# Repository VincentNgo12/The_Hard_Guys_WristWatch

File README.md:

View this project on [CADLAB.io](https://cadlab.io/project/29861). 

# Smart Wristwatch - The Hard Guys team

PCB schematics and hardware design for an ESP32-based wearable health and safety system.
This repository contains schematic capture, power architecture, and sensor integration
for a modular embedded prototype developed during a 48-hour hackathon.

> Status: Early schematic design

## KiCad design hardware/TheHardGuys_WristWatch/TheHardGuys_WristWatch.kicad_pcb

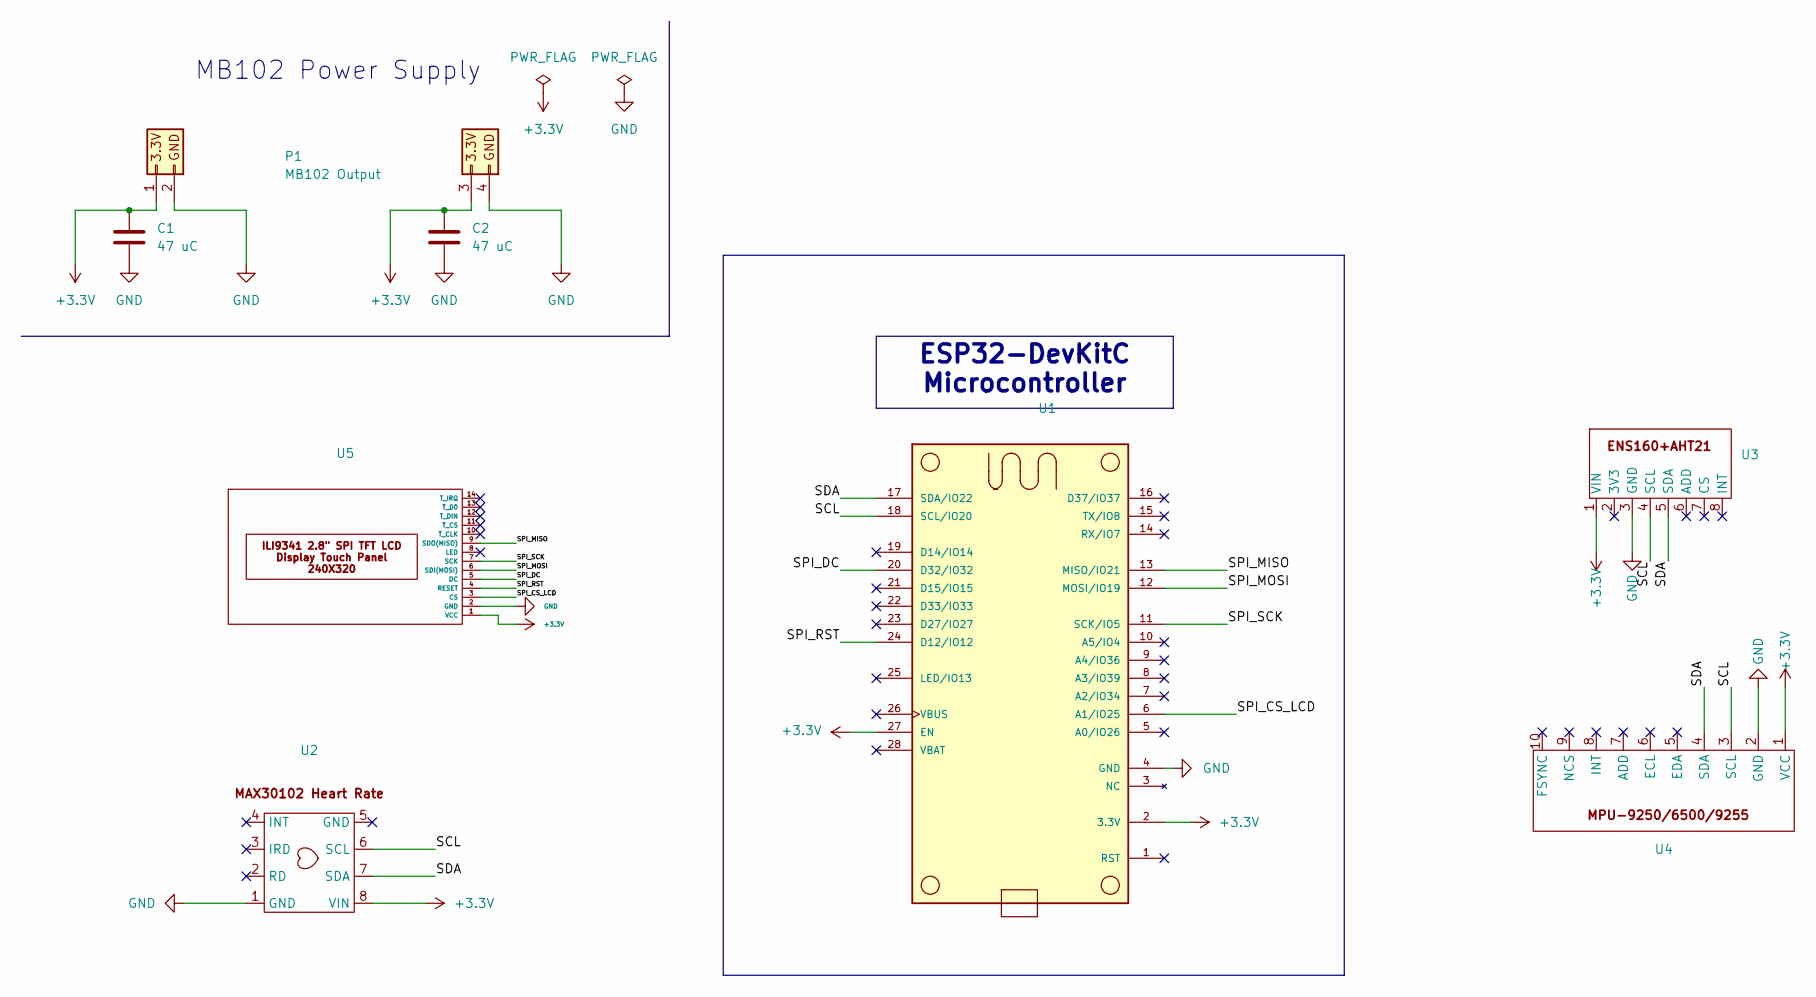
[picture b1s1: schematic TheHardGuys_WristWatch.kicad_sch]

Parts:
C1, C2: 47 uC; CP_Radial_D6.3mm_P2.50mm
P1: MB102 Output; MB102_Breadboard_Power_Module
U1: ESP32_Feather_V2
U2: MAX30102 Heart Rate_Pulse Sensor
U3: ENS160+AHT21_Environmental_Sensor
U4: MPU6500_IMU
U5: ILI9341_2.8__SPI_TFT_LCD

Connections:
+3.3V: C1.1, C2.1, P1.1 (3.3V), P1.3 (3.3V), U1.2 (3.3V), U1.27 (EN), U2.8 (VIN), U3.1 (VIN), U4.1 (VCC), U5.1 (VCC)
/SCL: U1.18 (SCL/IO20), U2.6 (SCL), U3.4 (SCL), U4.3 (SCL)
/SDA: U1.17 (SDA/IO22), U2.7 (SDA), U3.5 (SDA), U4.4 (SDA)
/SPI_CS_LCD: U1.6 (A1/IO25), U5.3 (CS)
/SPI_DC: U1.20 (D32/IO32), U5.5 (DC)
/SPI_MISO: U1.13 (MISO/IO21), U5.9 (SDO(MISO))
/SPI_MOSI: U1.12 (MOSI/IO19), U5.6 (SDI(MOSI))
/SPI_RST: U1.24 (D12/IO12), U5.4 (RESET)
/SPI_SCK: U1.11 (SCK/IO5), U5.7 (SCK)
GND: C1.2, C2.2, P1.2 (GND), P1.4 (GND), U1.4 (GND), U2.1 (GND), U3.3 (GND), U4.2 (GND), U5.2 (GND)

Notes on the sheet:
MB102 Power Supply
ESP32-DevKitC Microcontroller

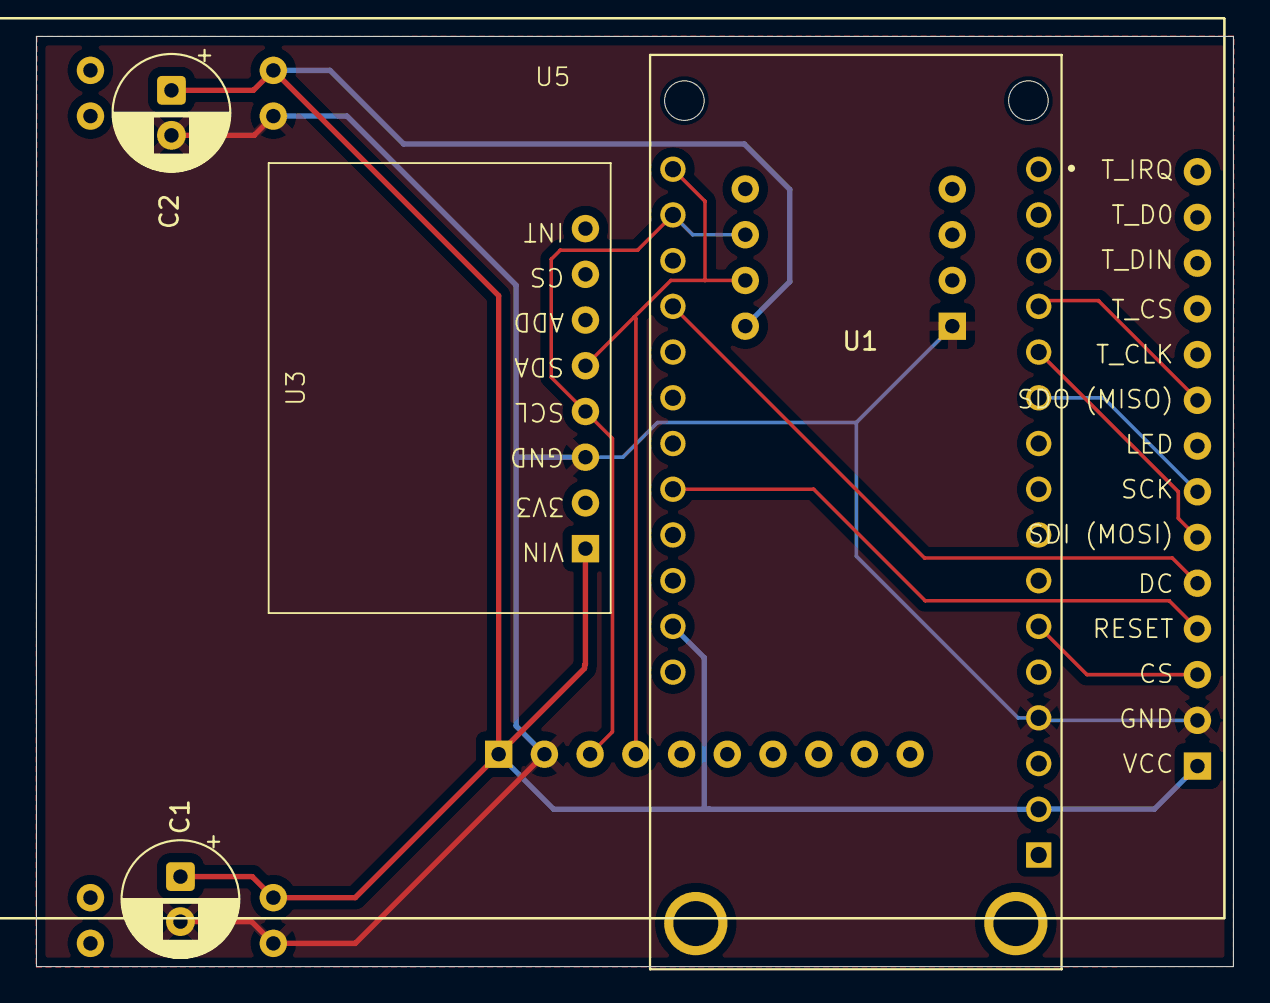
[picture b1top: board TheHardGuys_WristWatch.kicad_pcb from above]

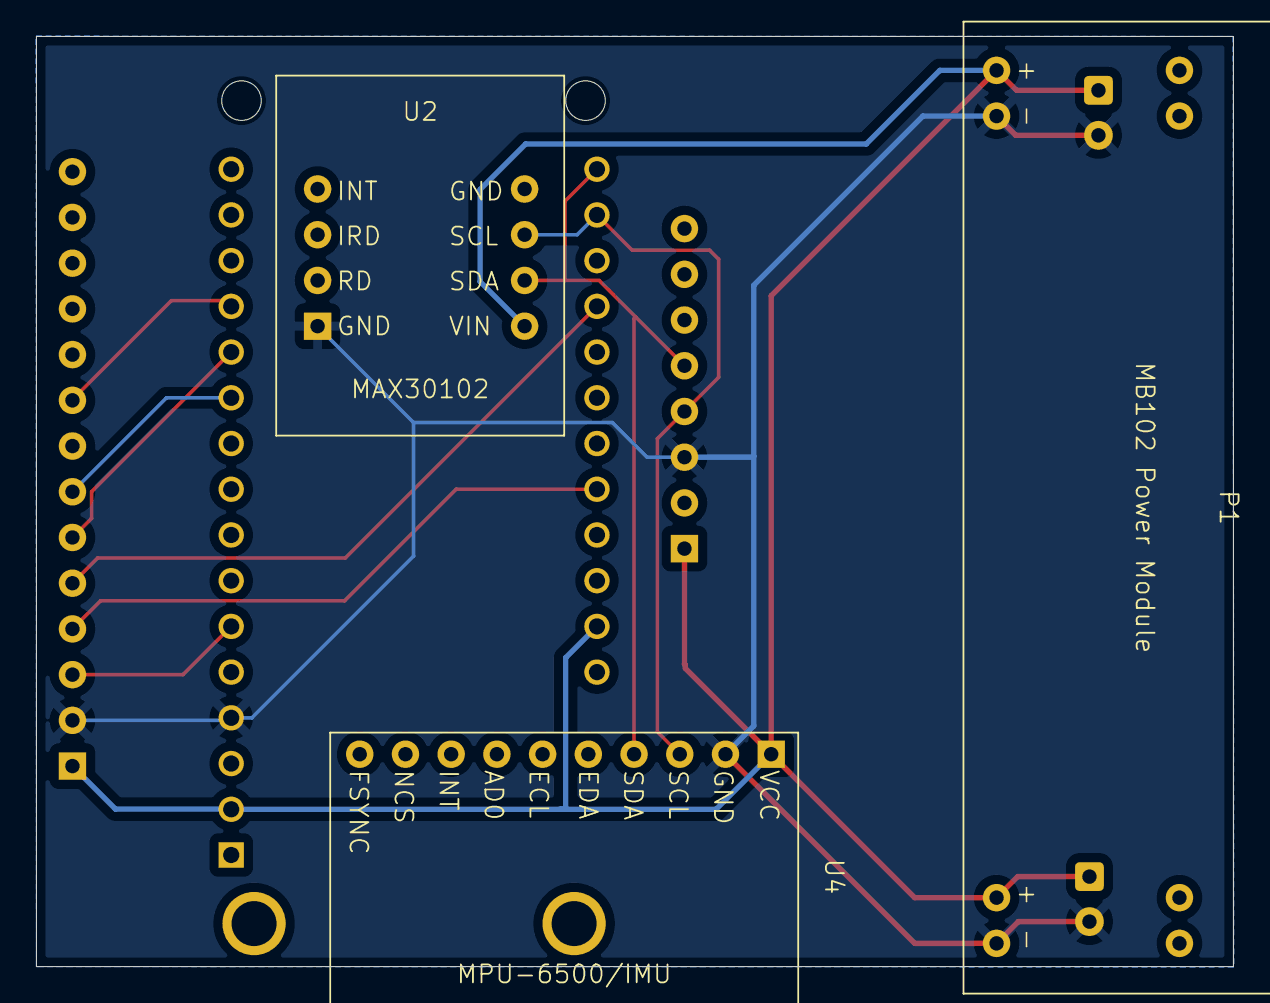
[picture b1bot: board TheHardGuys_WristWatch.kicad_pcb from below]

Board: 2 copper layers, 66.5 x 51.7 mm, 8 parts (3 on the bottom side), 10 nets.

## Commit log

2026-01-20 Backlink to CADLAB.io has been added.
2026-01-21 Initialize repo structure
2026-01-21 Added ESP32 symbol and footprints
2026-02-12 Passed ERC Tests
2026-02-13 Schematic Edited with EPS32 Feather V2. PCB Not updated
2026-02-14 Save Cause im scared
2026-02-14 Final Design PCB V-1.00
2026-02-14 applied manufacturing design capabilities
2026-02-14 Added Team Logo and Signatures on SilkScreen
2026-02-16 Initialize firmware development directory
